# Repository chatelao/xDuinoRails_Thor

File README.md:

# xDuinoRails-Thor-M

[Interactive Bill of Materials (iBOM)](https://chatelao.github.io/xDuinoRails_Thor/xDuinoRails-Thor-M-iBOM.html)

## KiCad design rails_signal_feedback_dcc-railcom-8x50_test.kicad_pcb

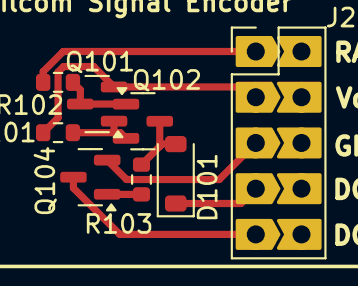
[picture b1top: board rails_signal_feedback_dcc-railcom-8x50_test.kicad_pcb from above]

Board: 2 copper layers, 8 parts (0 on the bottom side), 9 nets.

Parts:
D101: 1N5819W; D_SOD-123
J201: Conn_02x05_Odd_Even; PinHeaderJP_2x05_P2.54mm_Vertical
Q101, Q102: S8550; 8x50_SOT-23
Q104: S8050; 8x50_SOT-23
R101: 20R; R_0603_1608Metric
R102, R103: 10k; R_0603_1608Metric

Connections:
0: J201.5, Q104.1 (E)
/+J_3v3: J201.3, Q101.1 (E), R101.2
/J_DCC0: D101.1 (K), J201.7
/J_DCC1: J201.9, Q104.3 (C)
/J_RAILCOM_DATA: J201.1, R102.2
/rails_signal_feedback_dcc-railcom-8x50/RC_CURR: Q101.2 (B), Q102.1 (E), R101.1
/rails_signal_feedback_dcc-railcom-8x50/RC_DATA_IN: Q101.3 (C), Q102.2 (B), R102.1
/rails_signal_feedback_dcc-railcom-8x50/RC_SIGNAL: D101.2 (A), Q102.3 (C), R103.1
unnamed: Q104.2 (B), R103.2

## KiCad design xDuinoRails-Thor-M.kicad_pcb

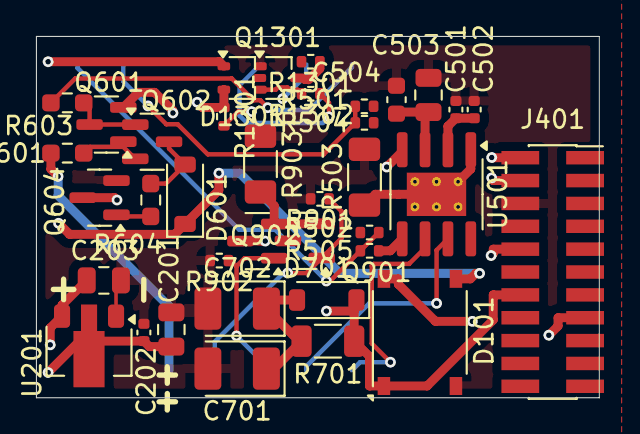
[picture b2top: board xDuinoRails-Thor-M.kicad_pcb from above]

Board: 6 copper layers, 31.3 x 20.1 mm, 38 parts (1 on the bottom side), 28 nets.

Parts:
C201: 22uF; C_0805_2012Metric
C202: 1u; C_0402_1005Metric
C203: 47uF; C_0805_2012Metric
C501: 100nF; C_0402_1005Metric
C502: 10uF; C_0402_1005Metric
C503: 10uF; C_0805_2012Metric
C504: 100nF; C_0603_1608Metric
C701, C702: 100uF; CP_EIA-3528-21_Kemet-B_Pad1.50x2.35mm_HandSolder
D101: ABS10; Diode_Bridge_Diotec_ABS
D601, D701: 1N5819W; D_SOD-123
D1301: BAT54CW; SOT-323_SC-70
J401: Conn_02x11_Odd_Even; PinSocket_2x11_P1.27mm_Vertical_SMD
Q601, Q602: S8550; 8x50_SOT-23
Q604: S8050; 8x50_SOT-23
Q901, Q902: BSS138; SOT-23
Q1301: BSS138W; SOT-323_SC-70
R501, R502: 6k8; R_0402_1005Metric
R503, R903: 0R1; R_1206_3216Metric_Pad1.30x1.75mm_HandSolder
R504, R505: 1k; R_0402_1005Metric
R601: 20R; R_0603_1608Metric_Pad0.98x0.95mm_HandSolder
R603, R604: 10k; R_0603_1608Metric_Pad0.98x0.95mm_HandSolder
R701: 100R; R_1206_3216Metric
R901, R902, R1302: 10k; R_0402_1005Metric
R1201: 33k; R_0402_1005Metric
R1301: 100R; R_0402_1005Metric
U201: HT75xx-1-SOT89; SOT-89-3
U501: BDR6133; SOIC-8-1EP_3.9x4.9mm_P1.27mm_EP2.41x3.3mm_ThermalVias
U1101: MOUDLE-SEEEDUINO-XIAO; XIAO_SMD

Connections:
/+3V3: C203.1, C501.1, C502.2, J401.22, Q601.1 (E), R601.2, U201.3 (VOUT), U501.2 (VCC), U1101.12 (3V3)
/+U: C201.1, C202.1, C503.1, C504.1, D101.1 (+), D701.1 (K), J401.14, R701.1, U201.2 (VIN), U501.3 (VM)
/AMP_FUNC0: J401.13, Q901.3 (D)
/AMP_FUNC1: J401.15, Q902.3 (D)
/AMP_MOTOR0: J401.10, R501.2, U501.4 (OUTA)
/AMP_MOTOR1: J401.8, R502.2, U501.5 (OUTB)
/DCC0: D101.3, D601.1 (K), D1301.1, J401.4
/DCC1: D101.4, D1301.2, J401.2, Q604.3 (C), R1201.1
/DCC_ACK: R1302.1, U1101.5 (PA8_A4_D4_SDA)
/DCC_MM_SIGNAL: R1201.2, U1101.6 (PA9_A5_D5_SCL)
/EMF_MOTOR0: R501.1, R504.1, U1101.2 (PA4_A1_D1)
/EMF_MOTOR1: R502.1, R505.1, U1101.1 (PA02_A0_D0)
/FUNC0: Q901.1 (G), R901.1, U1101.11 (PA6_A10_D10_MOSI)
/FUNC1: Q902.1 (G), R902.1, U1101.10 (PA5_A9_D9_MISO)
/I_FUNC: Q901.2 (S), Q902.2 (S), R903.2, U1101.4 (PA11_A3_D3)
/MOTOR0: U501.6 (INA), U1101.8 (PB09_A7_D7_RX)
/MOTOR1: U501.7 (INB), U1101.9 (PA7_A8_D8_SCK)
/RAILCOM_DATA: R603.2, U1101.7 (PB08_A6_D6_TX)
/rails_power-buffer/BUFF_U+: C701.1, C702.1, D701.2 (A), R701.2
/rails_signal_combined-medium/rails-signal-acknowledge_dcc/DCC+: D1301.3, R1301.2
/rails_signal_combined-medium/rails-signal-acknowledge_dcc/DCC+_DROP: Q1301.3 (C), R1301.1
/rails_signal_combined-medium/rails-signal-acknowledge_dcc/DCC_ACK_IN: Q1301.2 (B), R1302.2
/rails_signal_combined-medium/rails_signal_feedback_dcc-railcom-8x50/RC_CURR: Q601.2 (B), Q602.1 (E), R601.1
/rails_signal_combined-medium/rails_signal_feedback_dcc-railcom-8x50/RC_DATA_IN: Q601.3 (C), Q602.2 (B), R603.1
/rails_signal_combined-medium/rails_signal_feedback_dcc-railcom-8x50/RC_SIGNAL: D601.2 (A), Q602.3 (C), R604.1
GND: C201.2, C202.2, C203.2, C501.2, C502.1, C503.2, C504.2, C701.2, C702.2, D101.2 (-), J401.6, Q604.1 (E), Q1301.1 (E), R503.1, R504.2, R505.2, R901.2, R902.2, R903.1, U201.1 (GND), U1101.13 (GND)
unnamed: Q604.2 (B), R604.2
PGND: R503.2, U501.1 (GND), U501.9 (PGND), U1101.3 (PA10_A2_D2)

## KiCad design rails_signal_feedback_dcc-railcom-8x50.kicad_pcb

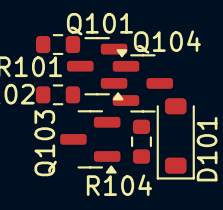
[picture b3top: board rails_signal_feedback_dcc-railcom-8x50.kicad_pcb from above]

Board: 2 copper layers, 7 parts (0 on the bottom side), 5 nets, no tracks yet.

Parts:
D101: 1N5819W; D_SOD-123
Q101, Q104: S8550; 8x50_SOT-23
Q103: S8050; 8x50_SOT-23
R101, R104: 10k; R_0603_1608Metric
R102: 20R; R_0603_1608Metric

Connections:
/+3V3: Q101.1 (E), R102.2
/RC_CURR: Q101.2 (B), Q104.1 (E), R102.1
/RC_DATA_IN: Q101.3 (C), Q104.2 (B), R101.1
/RC_SIGNAL: D101.2 (A), Q104.3 (C), R104.1
unnamed: Q103.2 (B), R104.2

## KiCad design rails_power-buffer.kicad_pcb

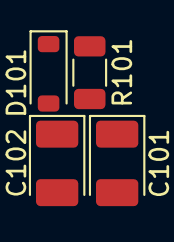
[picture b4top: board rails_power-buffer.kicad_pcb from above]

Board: 2 copper layers, 4 parts (0 on the bottom side), 3 nets, no tracks yet.

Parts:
C101, C102: 100uF; CP_EIA-3528-21_Kemet-B_Pad1.50x2.35mm_HandSolder
D101: 1N5819W; D_SOD-123
R101: 100R; R_1206_3216Metric

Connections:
/BUFF_U+: C101.1, C102.1, D101.2 (A), R101.2
/GND: C101.2, C102.2
/U+: D101.1 (K), R101.1

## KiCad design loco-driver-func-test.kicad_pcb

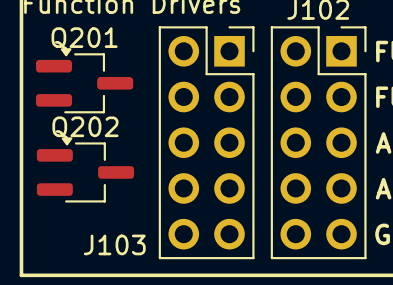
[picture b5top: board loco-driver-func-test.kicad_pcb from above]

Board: 2 copper layers, 4 parts (0 on the bottom side), 5 nets, no tracks yet.

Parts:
J102, J103: Conn_02x05_Odd_Even; PinSocket_2x05_P2.54mm_Vertical
Q201, Q202: AO3400A; SOT-23W_Handsoldering

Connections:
/J_AMP_FUNC0: J102.6, J103.5, J103.6, Q201.3 (D)
/J_AMP_FUNC1: J102.8, J103.7, J103.8, Q202.3 (D)
/J_FUNC0: J102.2, J103.1, J103.2, Q201.1 (G)
/J_FUNC1: J102.4, J103.3, J103.4, Q202.1 (G)
GND: J102.10, J103.9, J103.10, Q201.2 (S), Q202.2 (S)

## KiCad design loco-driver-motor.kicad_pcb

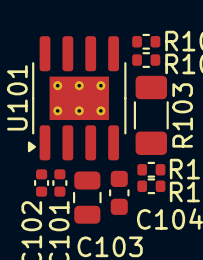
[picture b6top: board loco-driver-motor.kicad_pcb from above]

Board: 2 copper layers, 10 parts (0 on the bottom side), 8 nets, no tracks yet.

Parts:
C101: 100nF; C_0402_1005Metric
C102: 10uF; C_0402_1005Metric
C103: 10uF; C_0805_2012Metric
C104: 100nF; C_0603_1608Metric
R101, R102: 6k8; R_0402_1005Metric
R103: 0R1; R_1206_3216Metric_Pad1.30x1.75mm_HandSolder
R104, R105: 1k; R_0402_1005Metric
U101: BDR6133; SOIC-8-1EP_3.9x4.9mm_P1.27mm_EP2.41x3.3mm_ThermalVias

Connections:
/+3V3: C101.1, C102.2, U101.2 (VCC)
/AMP_MOTOR0: R101.2, U101.4 (OUTA)
/AMP_MOTOR1: R102.2, U101.5 (OUTB)
/EMF_MOTOR0: R101.1, R104.1
/EMF_MOTOR1: R102.1, R105.1
/GND: C101.2, C102.1, C103.2, C104.2, R103.1, R104.2, R105.2
/U+: C103.1, C104.1, U101.3 (VM)
PGND: R103.2, U101.1 (GND), U101.9 (PGND)

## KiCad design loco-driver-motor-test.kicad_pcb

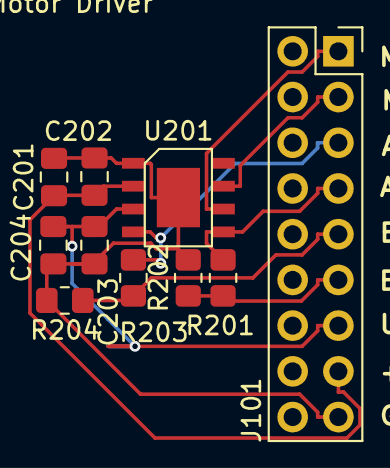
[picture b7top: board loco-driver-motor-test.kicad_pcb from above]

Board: 2 copper layers, 10 parts (0 on the bottom side), 9 nets.

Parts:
C201, C203: 10uF; C_0805_2012Metric_Pad1.18x1.45mm_HandSolder
C202, C204: 100nF; C_0805_2012Metric_Pad1.18x1.45mm_HandSolder
J101: Conn_02x09_Odd_Even; PinSocket_2x09_P2.54mm_Vertical
R201, R203: 6k8; R_0805_2012Metric_Pad1.20x1.40mm_HandSolder
R202, R204: 1k; R_0805_2012Metric_Pad1.20x1.40mm_HandSolder
U201: BDR6133

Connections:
/J_+3v3: C201.1, C202.1, J101.15, U201.2 (VCC)
/J_AMP_MOTOR0: J101.5, R203.2, U201.4 (OUTA)
/J_AMP_MOTOR1: J101.7, R201.2, U201.5 (OUTB)
/J_EMF_MOTOR0: J101.9, R203.1, R204.1
/J_EMF_MOTOR1: J101.11, R201.1, R202.1
/J_MOTOR0: J101.1, U201.6 (INA)
/J_MOTOR1: J101.3, U201.7 (INB)
/J_U+: C203.1, C204.1, J101.13, U201.3 (VM)
PGND: C201.2, C202.2, C203.2, C204.2, J101.17, R202.2, R204.2, U201.1 (GND), U201.9 (PGND)

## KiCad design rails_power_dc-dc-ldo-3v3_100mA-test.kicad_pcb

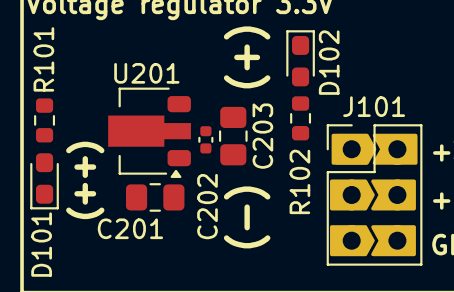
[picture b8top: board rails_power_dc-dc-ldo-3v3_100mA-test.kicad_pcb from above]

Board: 2 copper layers, 9 parts (0 on the bottom side), 5 nets, no tracks yet.

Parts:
C201, C203: 47uF; C_0805_2012Metric_Pad1.18x1.45mm_HandSolder
C202: 1u; C_0402_1005Metric
D101: LED_RED; LED_0603_1608Metric_Pad1.05x0.95mm_HandSolder
D102: LED_GREEN; LED_0603_1608Metric_Pad1.05x0.95mm_HandSolder
J101: Conn_02x03_Odd_Even; PinHeaderJP_2x03_P2.54mm_Vertical
R101, R102: 1k; R_0603_1608Metric
U201: HT75xx-1-SOT89; SOT-89-3

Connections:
/J_3v3: C203.1, J101.1, R102.1, U201.3 (VOUT)
/J_GND: C201.2, C202.2, C203.2, D101.1 (K), D102.1 (K), J101.5, U201.1 (GND)
/J_U+: C201.1, C202.1, J101.3, R101.1, U201.2 (VIN)
unnamed: D101.2 (A), R101.2
unnamed: D102.2 (A), R102.2

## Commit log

2026-01-06 feat: Add GitHub workflow for DRC and ERC checks
    This change adds a GitHub workflow to automatically run Design Rule Checks (DRC) and Electrical Rule Checks (ERC) on the KiCad project files. The workflow is triggered on push and pull request events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
2026-01-06 feat: Show ERC/DRC reports in build logs
    Modified the GitHub Actions workflow to always display the ERC and DRC reports in the build logs.
    The `kicad-cli` commands for ERC and DRC checks are updated to:
    - Use the `--output` flag to save the report to a file.
    - Use the `--exit-code-violations` flag to return a non-zero exit code if violations are found.
    - The script now captures the exit code, prints the contents of the report file to stdout, and then exits with the captured code.
    This ensures that developers can immediately see the details of any violations in the build logs, while still correctly marking the CI job as failed.
2026-01-06 feat: Update KiCad CI workflow to use modern action
    Replaced the deprecated `actions-for-kicad/setup-kicad` action with the recommended `actions-for-kicad/kicad-actions`.
    This new action is container-based, which improves performance by leveraging Docker layer caching and simplifies the workflow by removing the need for manual `kicad-cli` commands. The action is now c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
2026-01-06 feat: Refactor CI to use KiBot for ERC/DRC
    Replaced the `actions-for-kicad/kicad-actions` GitHub Action with `INTI-CMNB/KiBot` to run ERC and DRC checks.
    - Added a `kibot.yaml` to configure KiBot.
    - Enabled caching for 3D models to speed up the workflow.
2026-01-06 Fix: Correct KiBot preflight configuration
    The `kibot.yaml` file was using deprecated options for ERC and DRC checks, causing the CI to fail.
    This commit updates the `kibot.yaml` to use the correct `erc` and `drc` options for the preflight checks, and removes the unsupported `erc_warnings` and `drc_warnings` options.
2026-01-06 add missing file
2026-01-06 Fix: Correct KiBot preflight configuration
    The `kibot.yaml` file was using deprecated options for ERC and DRC checks, causing the CI to fail.
    This commit updates the `kibot.yaml` to use the correct `erc` and `drc` options for the preflight checks. The warning flags have been commented out, and `check_zone_fills` and `ignore_unconnected` ha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
2026-01-06 Chg - Clearer PCB layout
2026-01-06 Fix: Update KiBot configuration to use preflight checks
    The KiBot configuration is updated to use the `preflight` section for running ERC and DRC checks, which is the correct syntax for KiCad 8. The previous configuration was using the deprecated `outputs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
2026-01-06 Refactor preflight checks into ERC and DRC sections
    Replaced preflight checks with structured ERC and DRC sections.
2026-01-06 Change output directory from Documentation to gen_docs
2026-01-06 Remove targets configuration from kicad-checks.yml
2026-01-06 Update workflow to commit and push documentation
    Replaced KiBot action with git-auto-commit-action to automate documentation updates.
2026-01-06 Add KiBot step to KiCad checks workflow
2026-01-06 Add write permissions to kicad-checks workflow
    Added permissions for the action to write to the repository.
2026-01-06 Update KiCad checks workflow to upload artifacts
    Replaced commit and push step with upload artifact step for documentation.
2026-01-06 Fix - ERC updates
2026-01-07 feat: Cache ngspice installation in CI
    This change introduces a caching step for the ngspice package in the
    .github/workflows/kicad-checks.yml workflow.
    The caching is implemented using the actions/cache action and a dynamic
    key based on the week number to ensure the cache is periodically
    updated. This will reduce the time it takes to run the CI checks by
    avoiding the need to download ngspice on every run.
2026-01-07 feat: Add ngspice netlist export to KiBot config
    This change updates the `kibot.yaml` configuration to include a new output that generates an ngspice-compatible SPICE netlist from the main schematic.
2026-01-07 feat(ci): Run KiBot for all KiCad projects
    This change refactors the KiCad CI workflow to dynamically run KiBot for every `.kicad_pro` file found in the repository root.
    Key changes:
    - Implemented a matrix strategy in `kicad-checks.yml` to discover all KiCad projects.
    - Configured the workflow to run a separate KiBot job for each project.
    - Updated the KiBot action to output artifacts to project-specific directories under the `assets/` folder.
    - Modified `kibot.yaml` to remove the hardcoded `gen_docs` prefix from output paths.
2026-01-07 feat: Add KiBot output for zipped gerber and drill files
    Adds a new `compress` output to `kibot.yaml` that creates a single zip archive containing all gerber and drill files.
    The files are placed at the root of the zip archive, without any subdirectories. This is achieved by setting the `dest` option to an empty string for each file source.
2026-01-07 feat: Add KiBot ZIP to releases
    Adds a new 'compress' output to kibot.yaml to create a ZIP archive of the generated documentation.
    Updates the GitHub Actions workflow to:
    - Trigger on tags starting with 'v'.
    - Create a GitHub Release.
    - Upload the generated ZIP file as a release asset.
2026-01-08 feat(ci): add pinion tool to docker image
    Adds the `pinion` tool to the Docker image used for CI checks.
    - Creates a `.github/Dockerfile` to build a custom image with `pinion` installed.
    - Modifies `.github/workflows/kicad-checks.yml` to build and use the custom image.
    - Adds a verification step to confirm the `pinion` installation.
2026-01-08 feat: Add pcbdraw output for board images
    Adds a new 'pcbdraw' output to the kibot.yaml configuration.
    This will generate a PNG image of each board, styled with 'oshpark-purple'.
    The image is saved as 'board_top.png' in the 'assets' directory,
    as required by the Pinion tool for pinout diagrams.
2026-01-08 Fix - Test für RC 8x50
2026-01-08 Fix - loco-driver-func (ERC)
2026-01-08 Fix - rail_signal_extract (ERC)
2026-01-08 Fix - Loco-driver-func
2026-01-08 Add - Libraries
2026-01-08 Fix - DRC errors in LDO test schematics
2026-01-08 Fix - Ac-Dc Bridge Medium test
2026-01-08 Fix - Ignore double power flags
2026-01-08 Fix - Exclude some low-level errors
2026-01-08 Fix - Unconnected lines excluded
2026-01-08 Fix - Annotation fix
2026-01-08 Fix - loco-driver-motor-tests pins
2026-01-08 Fix - Annotation gap
2026-01-08 Fix - Page number for annotations
2026-01-09 feat(ci): Consolidate KiBot results into a single release
    Refactor the GitHub Actions workflow to create a single release for all KiCad projects.
    Previously, a release was created for each project, which was not the desired behavior.
    The new implementation uses a separate 'release' job that depends on the successful completion of all 'check' jobs. This new job downloads all the artifacts and uploads them to a single release, ensu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
2026-01-11 feat: Add initial documentation concept
    Creates a new file at /documentation/DOCUMENTATION_CONCEPT.md to outline the structure and plan for user documentation.
2026-01-11 feat: Add AGPL-3.0-or-later license
    Adds a LICENSE file containing the GNU Affero General Public License v3.0 to the root of the repository.
2026-01-11 feat: Add Pinion to GH workflow
    - Extend the GH workflow to use pinion
    - Add Pinion to the `kicad-checks.yml` workflow
    - Install Pinion using pip
    - Add a step to run Pinion for projects with a `.pinion.yaml` file
    - Add a `pcbdraw` output to `kibot.yaml` to generate the board image required by Pinion
2026-01-13 fix(ci): Install Pillow dependencies to fix Pinion installation
    The installation of the `pinion` package was failing during the
    GitHub Actions `check` job. The root cause was that a dependency,
    `Pillow`, requires C libraries like `libjpeg` and `zlib` to be
    present on the system to build correctly from source.
    This commit resolves the issue by adding a new step to the workflow
    that uses `apt-get` to install the required development packages
2026-01-13 fix(ci): Run pinion inside KiBot container
    The pinion tool was failing with a 'ModuleNotFoundError' because it was running on the host runner, which does not have the required 'pcbnew' Python module.
    This change moves the installation and execution of pinion into the `pre_launch_script` and `post_launch_script` of the KiBot GitHub Action. This ensures that pinion runs within the same Docker conta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
2026-01-13 feat: Update documentation with each build
    - Create a minimal README.md with a link to the iBOM.html on Github-Pages
    - Publish xDuinoRails-Thor-M-schematic.pdf in the root
    - Publish xDuinoRails-Thor-M-iBOM.html on Github-Pages
    - Publish xDuinoRails-Thor-M-PCB*.pdf in the /documentations directory
    - Add a deploy job to the workflow to publish the iBOM to Github-Pages
    - Update the release job to publish the schematic and PCB PDFs to the release
